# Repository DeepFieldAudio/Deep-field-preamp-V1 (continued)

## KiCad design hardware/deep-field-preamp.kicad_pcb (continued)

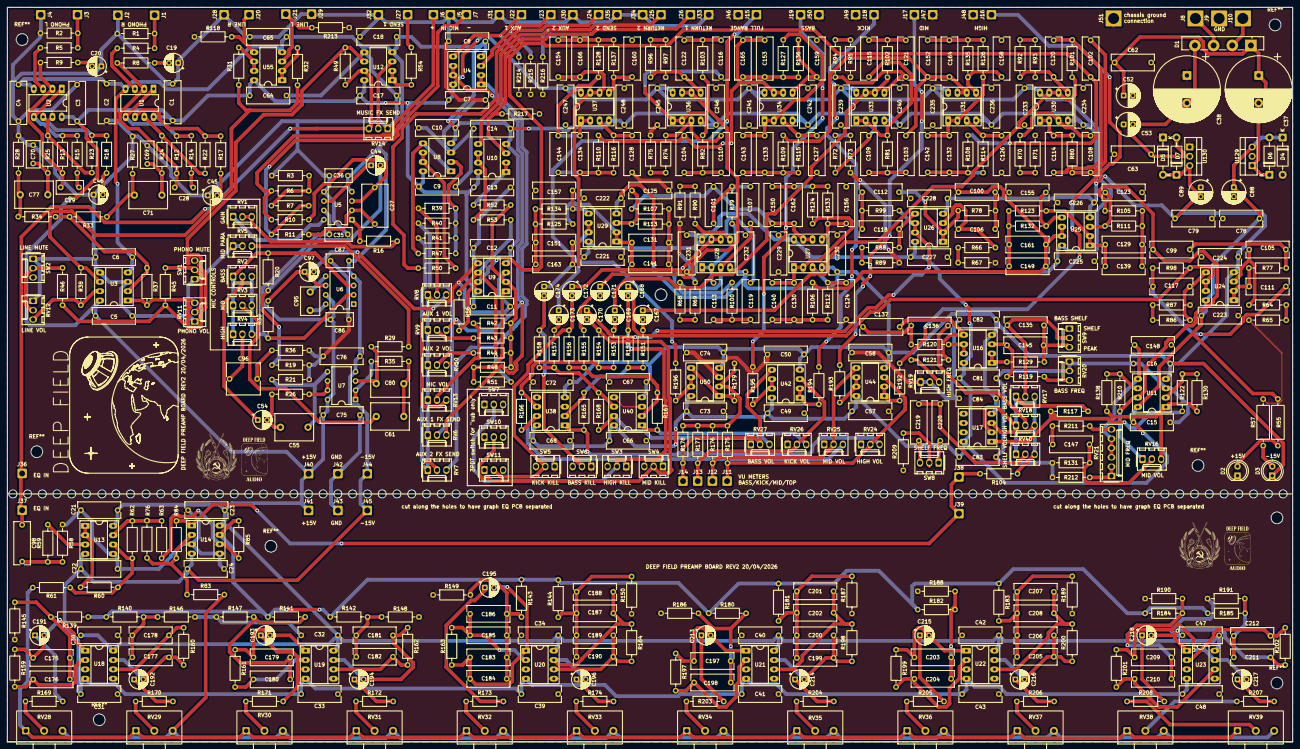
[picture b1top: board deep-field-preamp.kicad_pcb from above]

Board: 2 copper layers, 350.0 x 200.0 mm, 595 parts (0 on the bottom side), 308 nets.

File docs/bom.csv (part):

"Id";"Designator";"Footprint";"Quantity";"Designation";"Supplier and ref";
1;"C1, C2, C3, C4, C5, C6, C7, C8, C9, C10, C11, C12, C13, C14, C15, C16, C17, C18, C21, C22, C23, C24, C30, C31, C32, C33, C34, C39, C40, C41, C42, C43, C47, C48, C49, C50, C57, C58, C62, C63, C64, C65, C66, C67, C68, C72, C73, C74, C75, C76, C78, C79, C81, C82, C83, C84, C221, C222, C223, C224, C225, C226, C227, C228, C229, C230, C231, C232, C233, C234, C235, C236, C239, C240, C241, C242, C245, C246, C247, C248";"C_Rect_L11.5mm_W4.3mm_P10.00mm_MKT";80;"100nF";;;
2;"C19, C20, C45, C46, C54";"CP_Radial_D5.0mm_P2.50mm";5;"22uF";;;
3;"C27";"C_Rect_L11.5mm_W6.9mm_P10.00mm_MKT";1;"1nF";;;
4;"C28, C29";"C_Rect_L7.2mm_W3.5mm_P5.00mm_FKS2_FKP2_MKS2_MKP2";2;"22nF";;;
5;"C35, C36, C69, C70, C86, C87";"C_Rect_L7.2mm_W3.5mm_P5.00mm_FKS2_FKP2_MKS2_MKP2";6;"100nF";;;
6;"C37, C38";"CP_Radial_D18.0mm_P7.50mm";2;"4700u";;;
7;"C44, C97, C191, C192, C193, C194, C195, C196, C213, C214, C215, C216, C217, C218";"CP_Radial_D5.0mm_P2.50mm";14;"10uF";;;
8;"C52, C53, C88, C89";"CP_Radial_D6.3mm_P2.50mm";4;"100uF";;;
9;"C55";"C_Rect_L10.3mm_W7.2mm_P7.50mm_MKS4";1;"68nF";;;
10;"C61";"C_Rect_L10.3mm_W7.2mm_P7.50mm_MKS4";1;"82nF";;;
11;"C71, C77";"C_Rect_L10.3mm_W7.2mm_P7.50mm_MKS4";2;"1uF";;;
12;"C80";"C_Rect_L10.3mm_W7.2mm_P7.50mm_MKS4";1;"10nF";;;
13;"C95";"C_Disc_D7.5mm_W5.0mm_P5.00mm";1;"22pF";;;
14;"C96";"C_Rect_L9.0mm_W8.5mm_P7.50mm_MKT";1;"22nF";;;
15;"C98";"C_Rect_L11.5mm_W4.3mm_P10.00mm_MKT";1;"1uF unpolarized";;;
16;"C99, C102, C105, C108, C111, C114, C117, C120, C123, C126, C129, C132, C139, C142, C149, C152, C155, C158, C161, C164, C188, C189, C203, C204";"C_Rect_L11.5mm_W4.3mm_P10.00mm_MKT";24;"27nF";;;
17;"C100, C103, C106, C109, C112, C115, C118, C121, C124, C127, C130, C133, C140, C143, C150, C153, C156, C159, C162, C165, C197, C198, C200, C201";"C_Rect_L11.5mm_W4.3mm_P10.00mm_MKT";24;"47nF";;;
18;"C101, C104, C107, C110, C113, C116, C119, C122, C125, C128, C131, C134, C141, C144, C151, C154, C157, C160, C163, C166, C219";"C_Rect_L11.5mm_W4.3mm_P10.00mm_MKT";21;"22nF";;;
19;"C135";"C_Rect_L11.5mm_W4.3mm_P10.00mm_MKT";1;"470nF";;;
20;"C136, C206, C207, C220";"C_Rect_L11.5mm_W4.3mm_P10.00mm_MKT";4;"12nF";;;
21;"C137";"C_Rect_L11.5mm_W4.3mm_P10.00mm_MKT";1;"33pF";;;
22;"C145";"C_Rect_L11.5mm_W4.3mm_P10.00mm_MKT";1;"39nF";;;
23;"C147, C148";"C_Rect_L11.5mm_W4.3mm_P10.00mm_MKT";2;"33nF";;;
24;"C167, C168, C169, C170, C171, C172, C173, C174";"CP_Radial_D5.0mm_P2.50mm";8;"10µF";;;
25;"C175, C176";"C_Rect_L11.5mm_W4.3mm_P10.00mm_MKT";2;"220nF";;;
26;"C177, C178";"C_Rect_L11.5mm_W4.3mm_P10.00mm_MKT";2;"180nF";;;
27;"C179, C180";"C_Rect_L11.5mm_W4.3mm_P10.00mm_MKT";2;"150nF";;;
28;"C181, C182";"C_Rect_L11.5mm_W4.3mm_P10.00mm_MKT";2;"120nF";;;
29;"C183, C186";"C_Rect_L11.5mm_W4.3mm_P10.00mm_MKT";2;"5.6nF";;;
30;"C184, C185";"C_Rect_L11.5mm_W4.3mm_P10.00mm_MKT";2;"56nF";;;
31;"C187, C190, C199, C202, C209, C210";"C_Rect_L11.5mm_W4.3mm_P10.00mm_MKT";6;"4.7nF";;;
32;"C205, C208";"C_Rect_L11.5mm_W4.3mm_P10.00mm_MKT";2;"1.8nF";;;
33;"C211, C212";"C_Rect_L11.5mm_W4.3mm_P10.00mm_MKT";2;"2.2nF";;;
34;"D1";"Diode_Bridge_Vishay_GBU";1;"GBU4A";;;
35;"D2, D3";"LED_D5.0mm";2;"LED";;;
36;"D4, D5, D6, D7";"D_DO-41_SOD81_P10.16mm_Horizontal";4;"1N4001";;;
37;"J1, J2, J3, J4, J5, J6, J7, J15, J16, J17, J18, J19, J20, J21, J22, J23, J24, J25, J26, J27, J28, J29, J30, J31, J32, J33, J34, J35, J36, J37, J38, J39, J40, J41, J42, J43, J44, J45, J46, J47, J48, J49, J50";"SolderWire-0.75sqmm_1x01_D1.25mm_OD2.3mm";43;"Conn_01x01_Pin";;;
38;"J8, J9, J10, J51";"SolderWire-2.5sqmm_1x01_D2.4mm_OD4.4mm";4;"Conn_01x01_Pin";;;
39;"J11, J12, J13, J14";"SolderWire-0.75sqmm_1x01_D1.25mm_OD2.3mm";4;"~";;;
40;"R1, R2";"R_Axial_DIN0207_L6.3mm_D2.5mm_P10.16mm_Horizontal";2;"47k";;;
41;"R3, R19, R22, R23, R27, R28, R58, R131";"R_Axial_DIN0207_L6.3mm_D2.5mm_P10.16mm_Horizontal";8;"100k";;;
42;"R4, R5, R6, R7";"R_Axial_DIN0207_L6.3mm_D2.5mm_P10.16mm_Horizontal";4;"2k2";;;
43;"R8, R9";"R_Axial_DIN0207_L6.3mm_D2.5mm_P10.16mm_Horizontal";2;"4k7";;;
44;"R10, R11";"R_Axial_DIN0207_L6.3mm_D2.5mm_P10.16mm_Horizontal";2;"220R";;;
45;"R12, R13";"R_Axial_DIN0207_L6.3mm_D2.5mm_P10.16mm_Horizontal";2;"180k";;;
46;"R14, R15, R31, R32, R33, R34, R37, R38, R39, R40, R41, R42, R43, R44, R45, R46, R47, R48, R49, R51, R52, R53, R56, R60, R62, R63, R66, R67, R72, R73, R76, R78, R81, R84, R88, R89, R94, R95, R99, R102, R106, R109, R112, R115, R118, R124, R127, R133, R136, R151, R152, R153, R154, R155, R156, R157, R158, R165, R166, R167, R168, R169, R170, R171, R172, R173, R174, R175, R176, R177, R178, R179, R203, R204, R205, R206, R207, R208, R213, R214, R215, R216, R217";"R_Axial_DIN0207_L6.3mm_D2.5mm_P10.16mm_Horizontal";83;"10k";;;
47;"R16, R50, R54, R192, R193, R194, R195, R196";"R_Axial_DIN0207_L6.3mm_D2.5mm_P10.16mm_Horizontal";8;"100R";;;
48;"R17, R18, R20, R30, R104, R117, R145, R147";"R_Axial_DIN0207_L6.3mm_D2.5mm_P10.16mm_Horizontal";8;"2k7";;;
49;"R21, R29, R68, R69, R74, R75, R79, R82, R90, R91, R96, R97, R100, R103, R107, R110, R113, R116, R121, R125, R128, R134, R137";"R_Axial_DIN0207_L6.3mm_D2.5mm_P10.16mm_Horizontal";23;"56k";;;
50;"R24, R25";"R_Axial_DIN0207_L6.3mm_D2.5mm_P10.16mm_Horizontal";2;"750R";;;
51;"R26, R35, R36, R209";"R_Axial_DIN0207_L6.3mm_D2.5mm_P10.16mm_Horizontal";4;"470R";;;
52;"R55, R57";"R_Axial_DIN0309_L9.0mm_D3.2mm_P12.70mm_Horizontal";2;"15k";;;
53;"R59, R64, R65, R70, R71, R77, R80, R86, R87, R92, R93, R98, R101, R105, R108, R111, R114, R123, R126, R132, R135, R211, R212";"R_Axial_DIN0207_L6.3mm_D2.5mm_P10.16mm_Horizontal";23;"1k";;;
54;"R61, R83";"R_Axial_DIN0207_L6.3mm_D2.5mm_P10.16mm_Horizontal";2;"10R";;;
55;"R85, R119";"R_Axial_DIN0207_L6.3mm_D2.5mm_P10.16mm_Horizontal";2;"39k";;;
56;"R120";"R_Axial_DIN0207_L6.3mm_D2.5mm_P10.16mm_Horizontal";1;"270R";;;
57;"R122, R130, R138, R149, R150, R181, R182, R183, R210";"R_Axial_DIN0207_L6.3mm_D2.5mm_P10.16mm_Horizontal";9;"5k6";;;
58;"R129";"R_Axial_DIN0207_L6.3mm_D2.5mm_P10.16mm_Horizontal";1;"1k8";;;
59;"R139, R140, R141, R142, R163, R164";"R_Axial_DIN0207_L6.3mm_D2.5mm_P10.16mm_Horizontal";6;"82k";;;
60;"R143, R144";"R_Axial_DIN0207_L6.3mm_D2.5mm_P10.16mm_Horizontal";2;"43k";;;
61;"R146, R148";"R_Axial_DIN0207_L6.3mm_D2.5mm_P10.16mm_Horizontal";2;"2.7k";;;
62;"R159, R160, R161, R162";"R_Axial_DIN0207_L6.3mm_D2.5mm_P10.16mm_Horizontal";4;"160k";;;
63;"R180";"R_Axial_DIN0207_L6.3mm_D2.5mm_P10.16mm_Horizontal";1;"13k";;;
64;"R184, R185";"R_Axial_DIN0207_L6.3mm_D2.5mm_P10.16mm_Horizontal";2;"8k2";;;
65;"R186";"R_Axial_DIN0207_L6.3mm_D2.5mm_P10.16mm_Horizontal";1;"2k";;;
66;"R187, R188, R189";"R_Axial_DIN0207_L6.3mm_D2.5mm_P10.16mm_Horizontal";3;"820R";;;
67;"R190, R191";"R_Axial_DIN0207_L6.3mm_D2.5mm_P10.16mm_Horizontal";2;"1k2";;;
68;"R197";"R_Axial_DIN0207_L6.3mm_D2.5mm_P10.16mm_Horizontal";1;"27k";;;
69;"R198, R199, R200";"R_Axial_DIN0207_L6.3mm_D2.5mm_P10.16mm_Horizontal";3;"12k";;;
70;"R201, R202";"R_Axial_DIN0207_L6.3mm_D2.5mm_P10.16mm_Horizontal";2;"18k";;;
71;"RV1, RV2, RV3, RV4, RV14, RV16, RV17, RV18, RV40";"Molex_KK-254_AE-6410-03A_1x03_P2.54mm_Vertical";9;"B10k";;;
72;"RV5";"Molex_KK-254_AE-6410-03A_1x03_P2.54mm_Vertical";1;"B1M";;;
73;"RV6, RV7, RV8, RV9, RV10, RV11, RV12, RV13";"Molex_KK-254_AE-6410-03A_1x03_P2.54mm_Vertical";8;"A10k";;;
74;"RV19";"Molex_KK-254_AE-6410-03A_1x03_P2.54mm_Vertical";1;"B100k";;;
75;"RV20";"Molex_KK-254_AE-6410-03A_1x03_P2.54mm_Vertical";1;"B470k";;;
76;"RV21";"Molex_KK-254_AE-6410-06A_1x06_P2.54mm_Vertical";1;"B10k";;;
77;"RV24, RV25, RV26, RV27";"Molex_KK-254_AE-6410-03A_1x03_P2.54mm_Vertical";4;"A50k";;;
78;"RV28, RV29, RV30, RV31, RV32, RV33, RV34, RV35, RV36, RV37, RV38, RV39";"potentiometer_Alpha_RV16AF41_Single_Horizontal";12;"B100k";;;
79;"SW1, SW2, SW3, SW4, SW5, SW6, SW7, SW8, SW9, SW10, SW11";"Molex_KK-254_AE-6410-03A_1x03_P2.54mm_Vertical";11;"SW_SPDT";;;
80;"U1, U2, U8, U10, U12, U55";"DIP-8_W7.62mm_LongPads";6;"NE5532";;;
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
